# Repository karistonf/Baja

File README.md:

# Baja

## Projeto Baja SAE UEM - Equipe Capibaja
O Projeto Capibaja é um projeto acadêmico que visa a construção de um carro off-road monoposto movido a gasolina. A parte elétrica do veículo é responsável pela coleta de dados do carro e pela interface com o piloto, incluindo o monitoramento de velocidade e rodagem, bem como a saúde dos demais componentes do veículo. Não cabe a elétrica a fabricação de injeção eletrônica.

# Capacidades e objetivos do projeto
## Coleta de dados
* Velocidade (individual por roda) 
* Rodagem
* Temperatura CVT e motor
* Coordenadas de GPS
* Nível de Combustível
* Tensão da bateria
* Pressão nos freios
* E o mais importante, uma fita de led estilosa

# Construção

No projeto Capibaja, adotamos uma abordagem descentralizada para a coleta de dados, utilizando várias pequenas placas denominadas "placas gerais" (você pode obter mais informações sobre elas nos diretórios deste commit). Cada sensor é conectado a um microcontrolador, que por sua vez possui acesso à rede CAN de todo o veículo. Essas placas gerais são específicas para cada sensor e têm a função de ler os dados do sensor e transmitir seu valor na rede CAN.

Além das placas gerais, haverá uma segunda placa PCB, chamamos ela de placa principal, acessível ao piloto. Essa placa contará com uma tela e botões, servindo como interface para exibir os dados do carro em tempo real.

# Placa geral
Por enquanto é um esboço
Essa será a placa que coletara os dados dos sensores

# Placa principal
Essa será a placa que mostrará ao piloto as informações necessárias

# À fazer
* Corrigir footprint SD Card, Display 128x64
* Colocar os botões no lado correto

# Adicionar

# Feito
* Can transmissor

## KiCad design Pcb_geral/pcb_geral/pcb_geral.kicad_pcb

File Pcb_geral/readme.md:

# Descrição da placa geral

## A placa geral será responsável por coletar estes dados:

Relacionando os sensores usados com o protocolo para leitura do sensor

* Velocidade -> Sensor Indutivo -> porta digital
* Sensor de combustível -> Sensor reed switch (desenvolvido pela nossa equipe) -> porta analógica
* Célula de carga -> Analógica
* Sensor de temperatura motor -> Analógica
* Acelerômetro e giroscópio -> I2C
* Sensor de temperatura CVT -> I2C
* GPS -> Serial
* Sensor de pressão do fluido de freio -> * falta escolher o sensor para definir *
* Radio Frequência -> SPI 

## O que foi feito

3/ago

* Foi implementado proteção contra excesso de corrente e tensão contrária.
* Adicionado os conectores para os sensores e dispositivos externos, posicionados, e serigrafia indicando corretamente as conexões.
* Foi arrumado a posição dos componentes do can
* Inseriu-se um conector tipo borne para conectar ao chicote do veículo

## Coisas à fazer

3/ago

* Colocar optoacoplador
* Exemplo de comunicação para GPS, e quais pinos conectar
* Confirmar pinos para comunicação I2C
* Exemplo e confirmar pinos para conectar a fita de led
* Usar fita de led 12V
* Verificar se a ligação do mosfet
* reduzir o tamanho do regulador de tensão de 5V (se dimensionado o consumo de corrente)
* desenhar o contorno da placa, e caixa para proteção

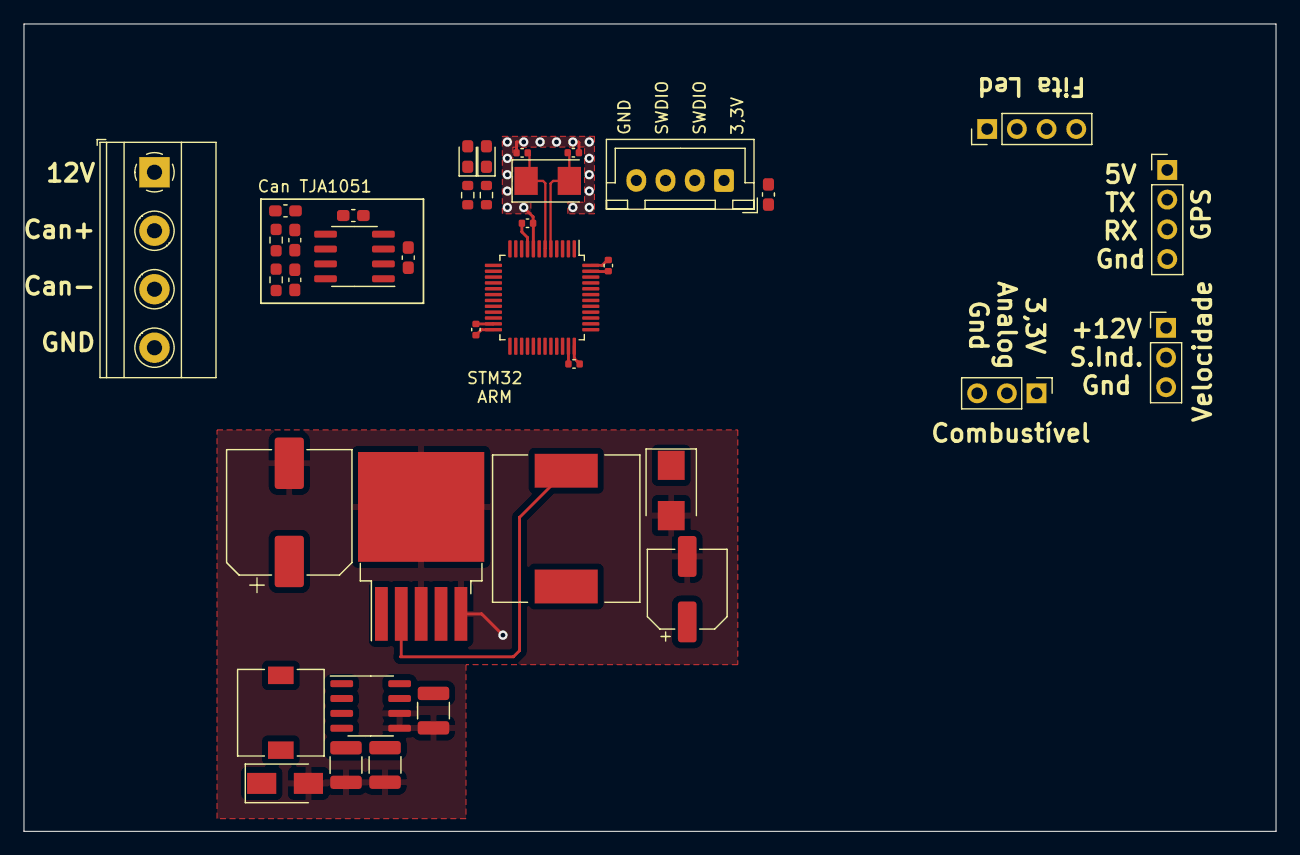
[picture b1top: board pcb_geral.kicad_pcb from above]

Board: 2 copper layers, 107.1 x 69.0 mm, 38 parts (0 on the bottom side), 14 nets.

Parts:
C1: 10uF; C_1210_3225Metric
C2: 680uF; CP_Elec_10x10.5
C3, C5: 100uF; C_1210_3225Metric
C4: 220uF; CP_Elec_6.3x5.4
C6: 100nF; C_0603_1608Metric_Pad1.08x0.95mm_HandSolder
C7: 47nF; C_0603_1608Metric_Pad1.08x0.95mm_HandSolder
C8: 100µF; C_0603_1608Metric_Pad1.08x0.95mm_HandSolder
C9, C10, C11, C12: 100µF; C_0402_1005Metric
C13, C14: 100pF; C_0603_1608Metric_Pad1.08x0.95mm_HandSolder
C15: 4,7uF; C_0603_1608Metric_Pad1.08x0.95mm_HandSolder
CC1, CC2: 33pF; C_0402_1005Metric
D1: D; D_SMA
D2: 1N5824; D_SMB
D3, D4: LED; LED_0603_1608Metric_Pad1.05x0.95mm_HandSolder
J1: Conn_01x04_Female; TerminalBlock_Phoenix_MKDS-1,5-4_1x04_P5.00mm_Horizontal
J2, J3: Conn_01x03_Female; PinHeader_1x03_P2.54mm_Vertical
J5, J6: Conn_01x04_Female; PinHeader_1x04_P2.54mm_Vertical
L1: 100uH; L_7.3x7.3_H4.5
L2: 33uH; L_12x12mm_H8mm
Prog1: Conn_01x04_Female; JST_XH_B4B-XH-A_1x04_P2.50mm_Vertical
R1, R2: 510; R_0603_1608Metric
R3, R4: 60; R_0603_1608Metric_Pad0.98x0.95mm_HandSolder
U1: LM2594M-3.3; SOIC-8_3.9x4.9mm_P1.27mm
U2: LM2596S-5; TO-263-5_TabPin3
U3: STM32F103C6Tx; LQFP-48_7x7mm_P0.5mm
U4: TJA1051T-3; SOIC-8_3.9x4.9mm_P1.27mm
Y2: 8Mhz; Crystal_SMD_5032-2Pin_5.0x3.2mm

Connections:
+3V3: C3.1, C5.1, C6.1, C8.1, C9.1, C10.1, C11.1, C12.1, D3.2 (A), D4.2 (A), L1.2, Prog1.1, U1.4 (FB), U3.9 (VDDA), U3.24 (VDD), U3.36 (VDD), U3.48 (VDD), U4.5 (VIO)
+5V: C4.1, C6.2, C7.1, J5.1, L2.2, U2.4 (FB), U4.3 (VCC)
+12V: C1.1, C2.1, J2.1, U1.7 (VIN), U2.1 (VIN)
/Can+: C13.2, J1.3, R3.1, U4.7 (CANH)
/Can-: C14.2, J1.2, R4.1, U4.6 (CANL)
/OSC+: CC2.1, U3.6 (PD1), Y2.1
/OSC-: CC1.1, U3.5 (PD0), Y2.2
/Out_pwr_indutor: D2.1 (K), L2.1, U2.2 (OUT)
GND: C1.2, C2.2, C3.2, C4.2, C5.2, C7.2, C8.2, C9.2, C10.2, C11.2, C12.2, C13.1, C14.1, C15.1, CC1.2, CC2.2, D1.2 (A), D2.2 (A), J1.4, J2.3, J5.4, Prog1.4, R2.2, U1.5 (~ON/OFF), U1.6 (GND), U2.3 (GND), U2.5 (~ON/OFF), U3.8 (VSSA), U3.23 (VSS), U3.35 (VSS), U3.47 (VSS), U4.2 (GND)
unnamed: C15.2, R3.2, R4.2
unnamed: D1.1 (K), L1.1, U1.8 (OUT)
unnamed: D3.1 (K), R1.2
unnamed: D4.1 (K), R2.1
PC13: R1.1, U3.2 (PC13)

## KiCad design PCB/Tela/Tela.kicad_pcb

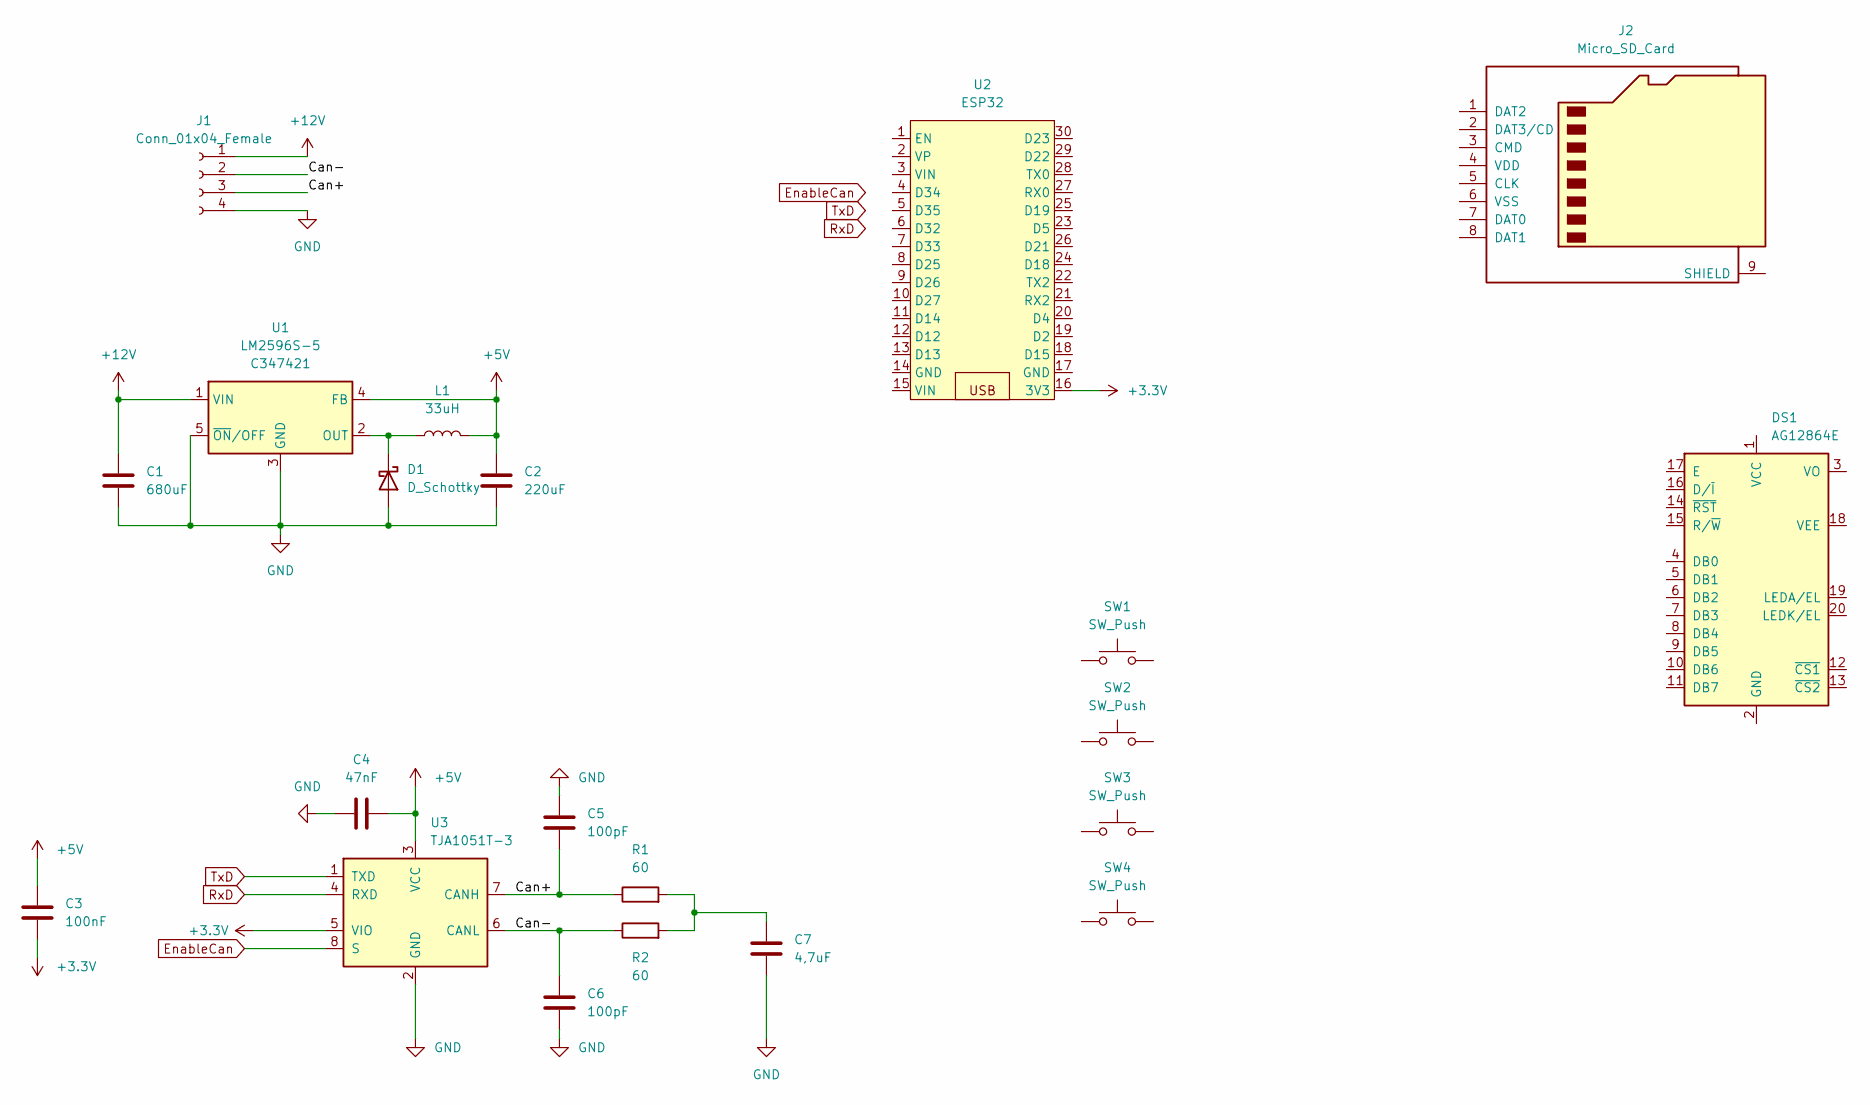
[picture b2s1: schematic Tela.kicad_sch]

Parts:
C1: 680uF; CP_Elec_10x10.5
C2: 220uF; CP_Elec_6.3x5.4
C3: 100nF; C_0603_1608Metric_Pad1.08x0.95mm_HandSolder
C4: 47nF; C_0603_1608Metric_Pad1.08x0.95mm_HandSolder
C5, C6: 100pF; C_0603_1608Metric_Pad1.08x0.95mm_HandSolder
C7: 4,7uF; C_0603_1608Metric_Pad1.08x0.95mm_HandSolder
D1: D_Schottky; D_SMB
DS1: AG12864E
J1: Conn_01x04_Female; TerminalBlock_Phoenix_MKDS-1,5-4-5.08_1x04_P5.08mm_Horizont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
J2: Micro_SD_Card; microSD_HC_Hirose_DM3D-SF
L1: 33uH; L_12x12mm_H8mm
R1, R2: 60; R_0603_1608Metric_Pad0.98x0.95mm_HandSolder
SW1, SW2, SW3, SW4: SW_Push; SW_SPST_PTS645
U1: LM2596S-5; TO-263-5_TabPin3; LCSC C347421
U2: ESP32; ESP32_DevKit
U3: TJA1051T-3; SOIC-8_3.9x4.9mm_P1.27mm

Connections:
+3.3V: C3.1, U2.16 (3V3), U3.5 (VIO)
+5V: C2.1, C3.2, C4.1, L1.2, U1.4 (FB), U3.3 (VCC)
+12V: C1.1, J1.1, U1.1 (VIN)
/Can+: C5.2, J1.3, R1.1, U3.7 (CANH)
/Can-: C6.2, J1.2, R2.1, U3.6 (CANL)
EnableCan: U3.8 (S)
GND: C1.2, C2.2, C4.2, C5.1, C6.1, C7.1, D1.2 (A), J1.4, U1.3 (GND), U1.5 (~ON/OFF), U3.2 (GND)
unnamed: C7.2, R1.2, R2.2
unnamed: D1.1 (K), L1.1, U1.2 (OUT)
RxD: U3.4 (RXD)
TxD: U3.1 (TXD)

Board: 2 copper layers, 21 parts (5 on the bottom side), 8 nets, no tracks yet.

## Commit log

2022-07-02 commit inicial, com primeiras atualizaçoes da pcb do baja 2023
2023-02-23 commit inicial da placa de uso geral do baja
2023-04-13 atualizacoes, sem grandes modificacoes
2023-04-27 cristal clock posicionado, seguindo as boas praticas de desenho de PCI
2023-04-27 plano de alimentação, saparar dos planos alimentação do plano digital
2023-06-23 foi adicionado o TJA1051 de can na placa. Falta os footprints e as conexão no microcontrolador
2023-06-23 adição dos footprint do modulo de can, adição dos botoes, e desenho de areas no silkscreen
2023-06-23 imagens
2023-06-23 placa geral, add can e footprints
2023-06-29 readme
2023-08-04 atualizacoes na placa geral, posicionamento do can, adição dos pontos para conexão para sensores e dispositivos externos, sistemas de proteção contra corrente excessiva e reversão de tensão, silk mai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
2023-11-10 gitignore
2023-11-17 prog can
2024-02-28 sinc
2024-06-13 add 3d
